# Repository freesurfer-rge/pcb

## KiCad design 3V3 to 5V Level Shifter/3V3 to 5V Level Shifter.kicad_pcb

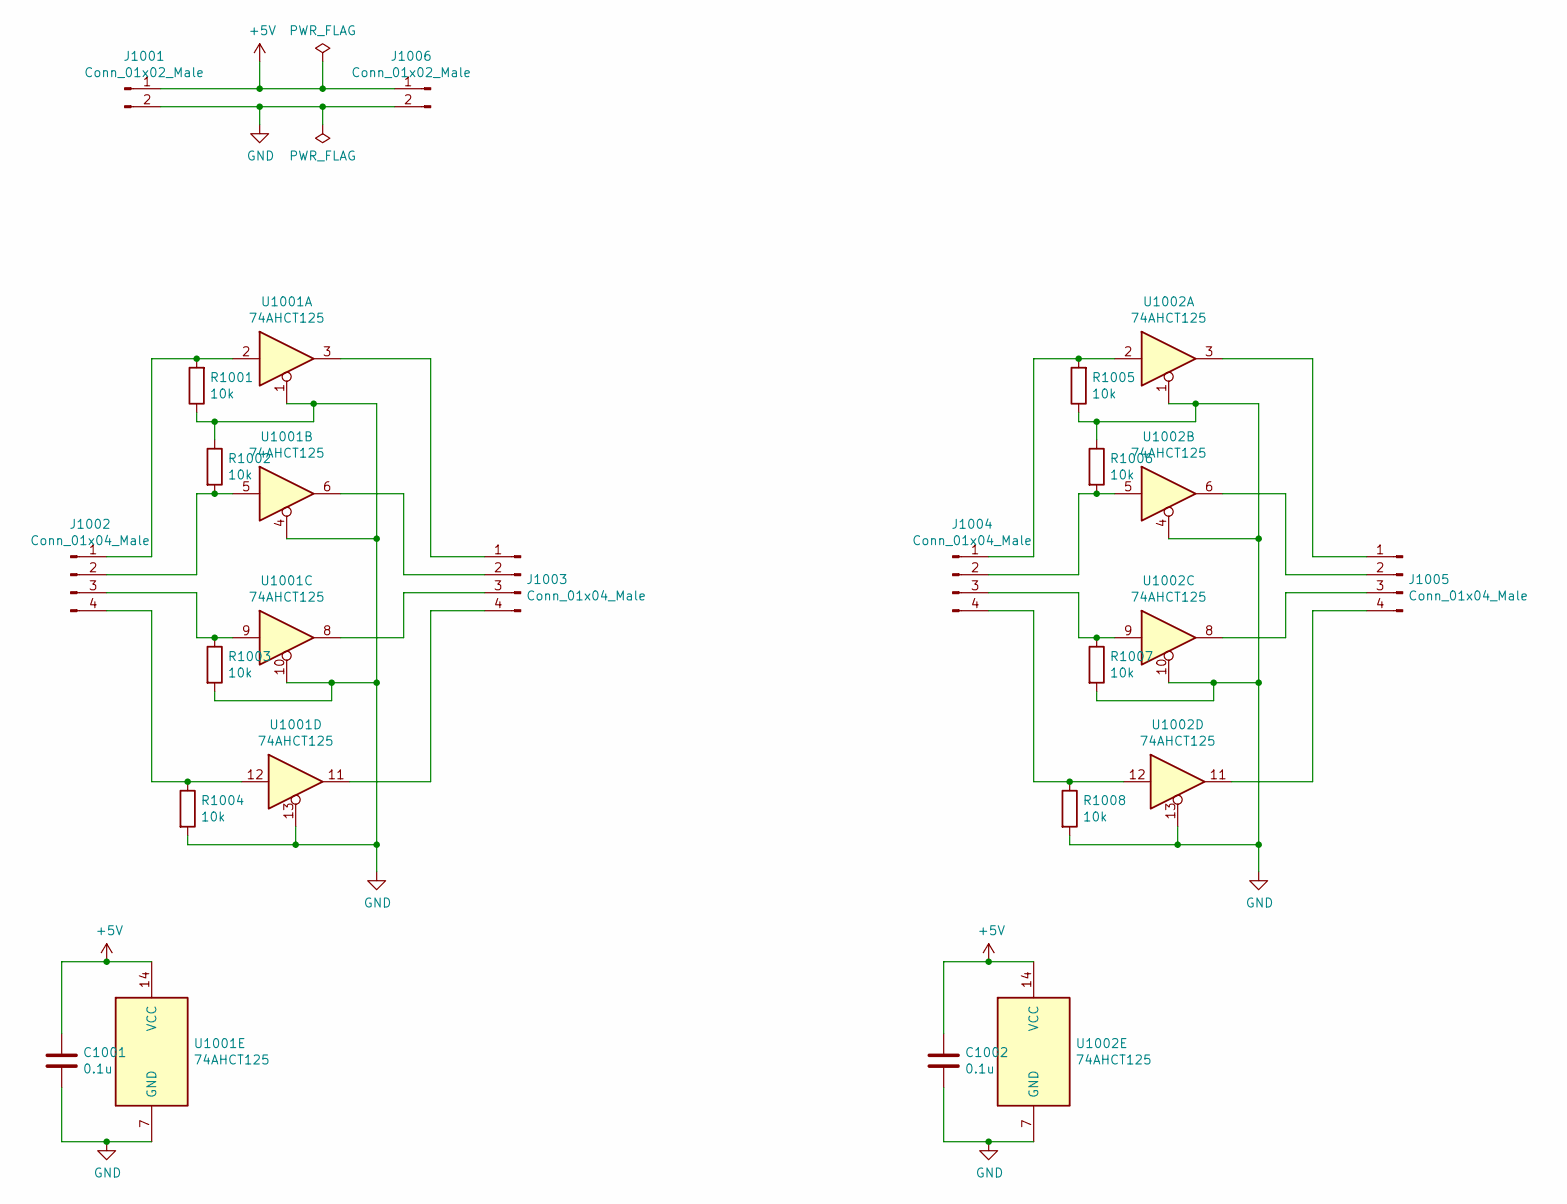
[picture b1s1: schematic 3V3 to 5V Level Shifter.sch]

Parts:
C1001, C1002: 0.1u; C_Disc_D4.7mm_W2.5mm_P5.00mm
J1001, J1006: Conn_01x02_Male; PinHeader_1x02_P2.54mm_Vertical
J1002, J1003, J1004, J1005: Conn_01x04_Male; PinHeader_1x04_P2.54mm_Vertical
R1001, R1002, R1003, R1004, R1005, R1006, R1007, R1008: 10k; R_Axial_DIN0207_L6.3mm_D2.5mm_P7.62mm_Horizontal
U1001, U1002: 74AHCT125; DIP-14_W7.62mm_Socket

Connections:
+5V: C1001.2, C1002.2, J1001.1, J1006.1, U1001.14 (VCC), U1002.14 (VCC)
GND: C1001.1, C1002.1, J1001.2, J1006.2, R1001.1, R1002.1, R1003.2, R1004.2, R1005.1, R1006.1, R1007.2, R1008.2, U1001.1, U1001.4, U1001.7 (GND), U1001.10, U1001.13, U1002.1, U1002.4, U1002.7 (GND), U1002.10, U1002.13
unnamed: J1002.1, R1001.2, U1001.2
unnamed: J1002.2, R1002.2, U1001.5
unnamed: J1002.3, R1003.1, U1001.9
unnamed: J1002.4, R1004.1, U1001.12
unnamed: J1003.1, U1001.3
unnamed: J1003.2, U1001.6
unnamed: J1003.3, U1001.8
unnamed: J1003.4, U1001.11
unnamed: J1004.1, R1005.2, U1002.2
unnamed: J1004.2, R1006.2, U1002.5
unnamed: J1004.3, R1007.1, U1002.9
unnamed: J1004.4, R1008.1, U1002.12
unnamed: J1005.1, U1002.3
unnamed: J1005.2, U1002.6
unnamed: J1005.3, U1002.8
unnamed: J1005.4, U1002.11

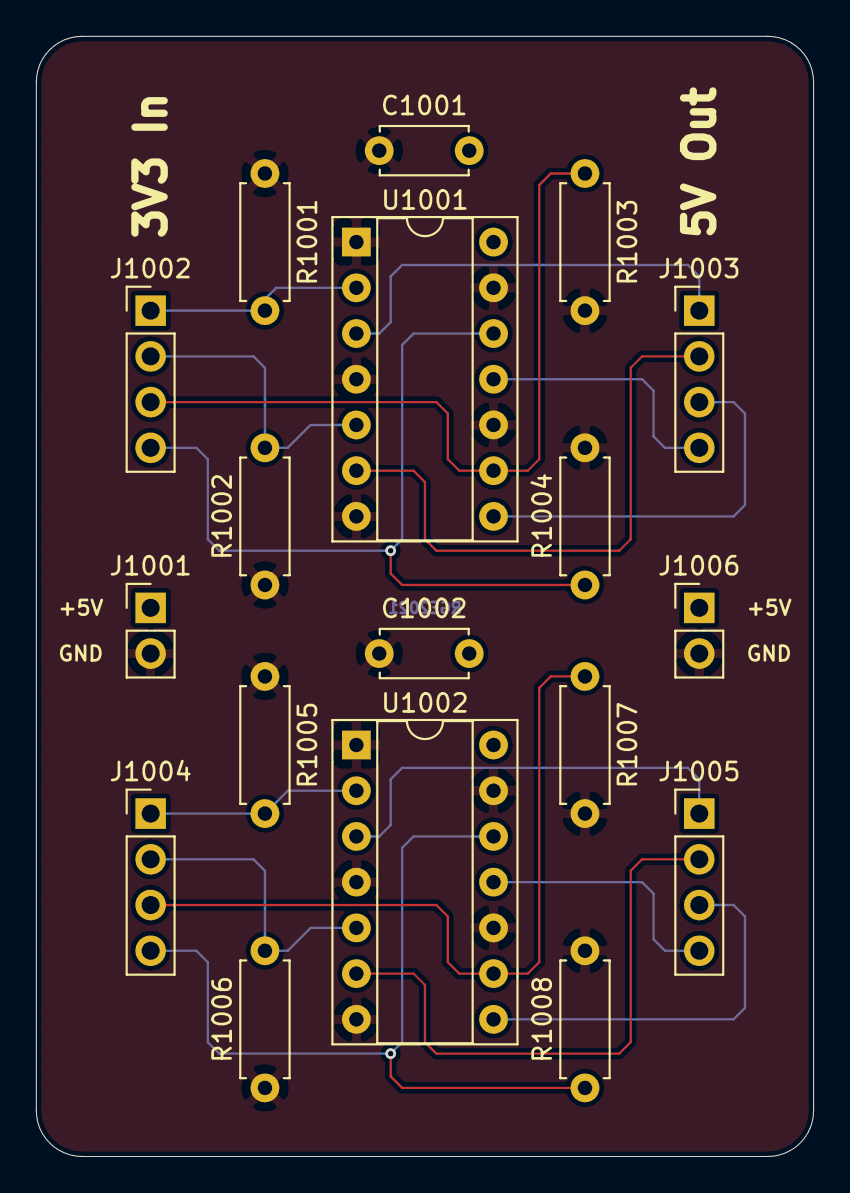
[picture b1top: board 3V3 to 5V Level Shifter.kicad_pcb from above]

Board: 2 copper layers, 43.2 x 62.2 mm, 18 parts (0 on the bottom side), 18 nets.

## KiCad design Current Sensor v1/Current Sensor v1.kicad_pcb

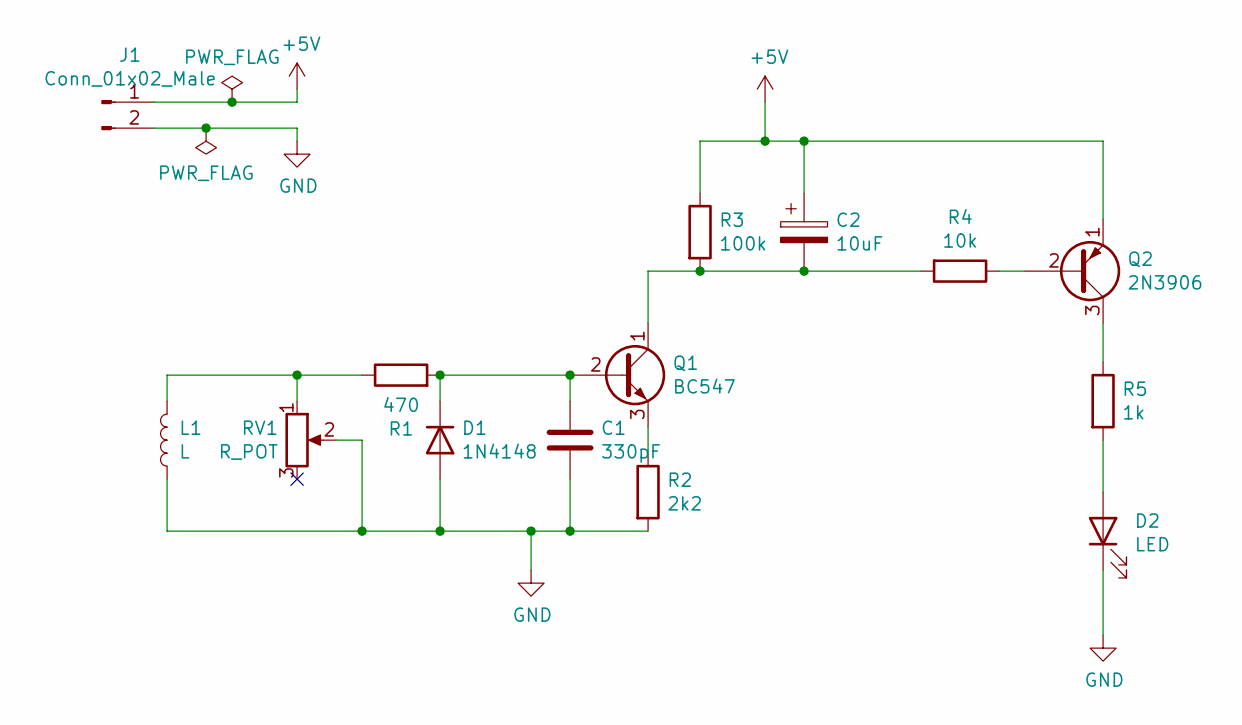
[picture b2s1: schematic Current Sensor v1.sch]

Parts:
C1: 330pF; C_Disc_D3.0mm_W2.0mm_P2.50mm
C2: 10uF; CP_Radial_D4.0mm_P1.50mm
D1: 1N4148; D_DO-35_SOD27_P7.62mm_Horizontal
D2: LED; LED_D5.0mm
J1: Conn_01x02_Male; PinHeader_1x02_P2.54mm_Vertical
L1: L; L_CS1050
Q1: BC547; TO-92_Inline_Wide
Q2: 2N3906; TO-92_Wide
R1: 470; R_Axial_DIN0207_L6.3mm_D2.5mm_P7.62mm_Horizontal
R2: 2k2; R_Axial_DIN0207_L6.3mm_D2.5mm_P7.62mm_Horizontal
R3: 100k; R_Axial_DIN0207_L6.3mm_D2.5mm_P7.62mm_Horizontal
R4: 10k; R_Axial_DIN0207_L6.3mm_D2.5mm_P7.62mm_Horizontal
R5: 1k; R_Axial_DIN0207_L6.3mm_D2.5mm_P7.62mm_Horizontal
RV1: R_POT; Potentiometer_Piher_PT-10-V10_Vertical

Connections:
+5V: C2.1, J1.1, Q2.1 (E), R3.1
GND: C1.2, D1.2 (A), D2.1 (K), J1.2, L1.1, R2.2, RV1.2
unnamed: C1.1, D1.1 (K), Q1.2 (B), R1.2
unnamed: C2.2, Q1.1 (C), R3.2, R4.2
unnamed: D2.2 (A), R5.2
unnamed: L1.2, R1.1, RV1.1
unnamed: Q1.3 (E), R2.1
unnamed: Q2.2 (B), R4.1
unnamed: Q2.3 (C), R5.1

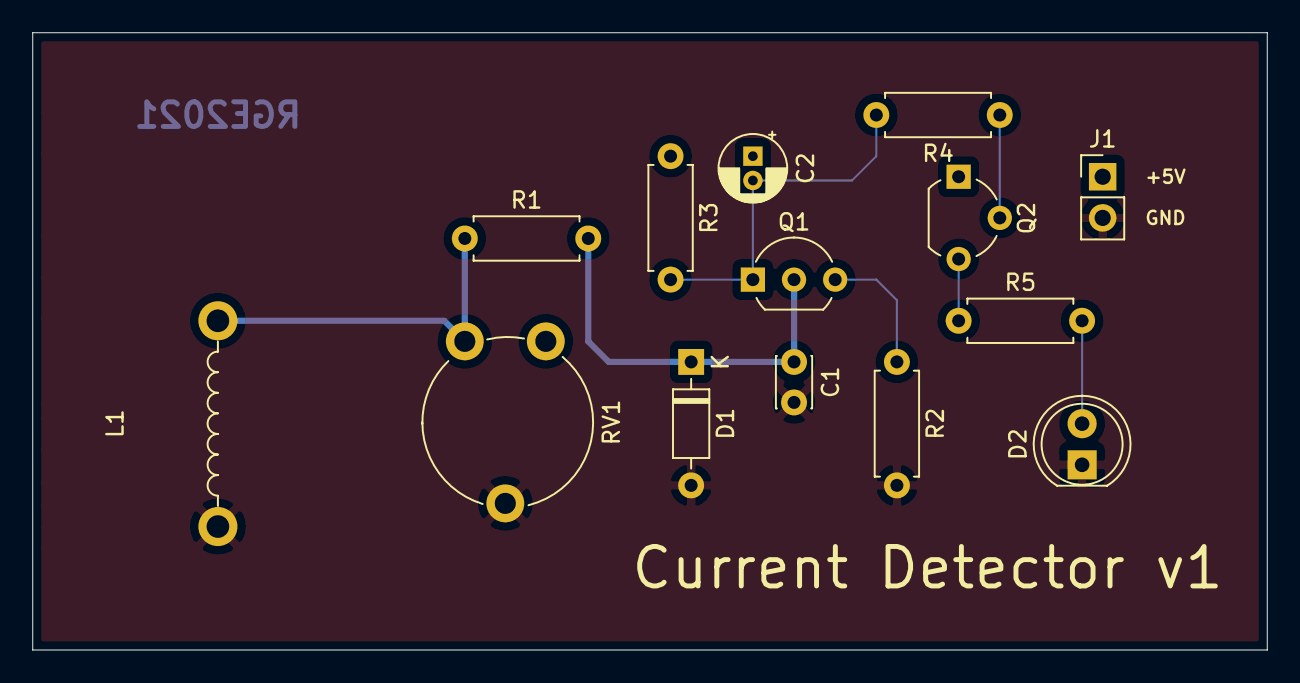
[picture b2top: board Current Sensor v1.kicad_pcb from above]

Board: 2 copper layers, 76.2 x 38.1 mm, 14 parts (0 on the bottom side), 9 nets.

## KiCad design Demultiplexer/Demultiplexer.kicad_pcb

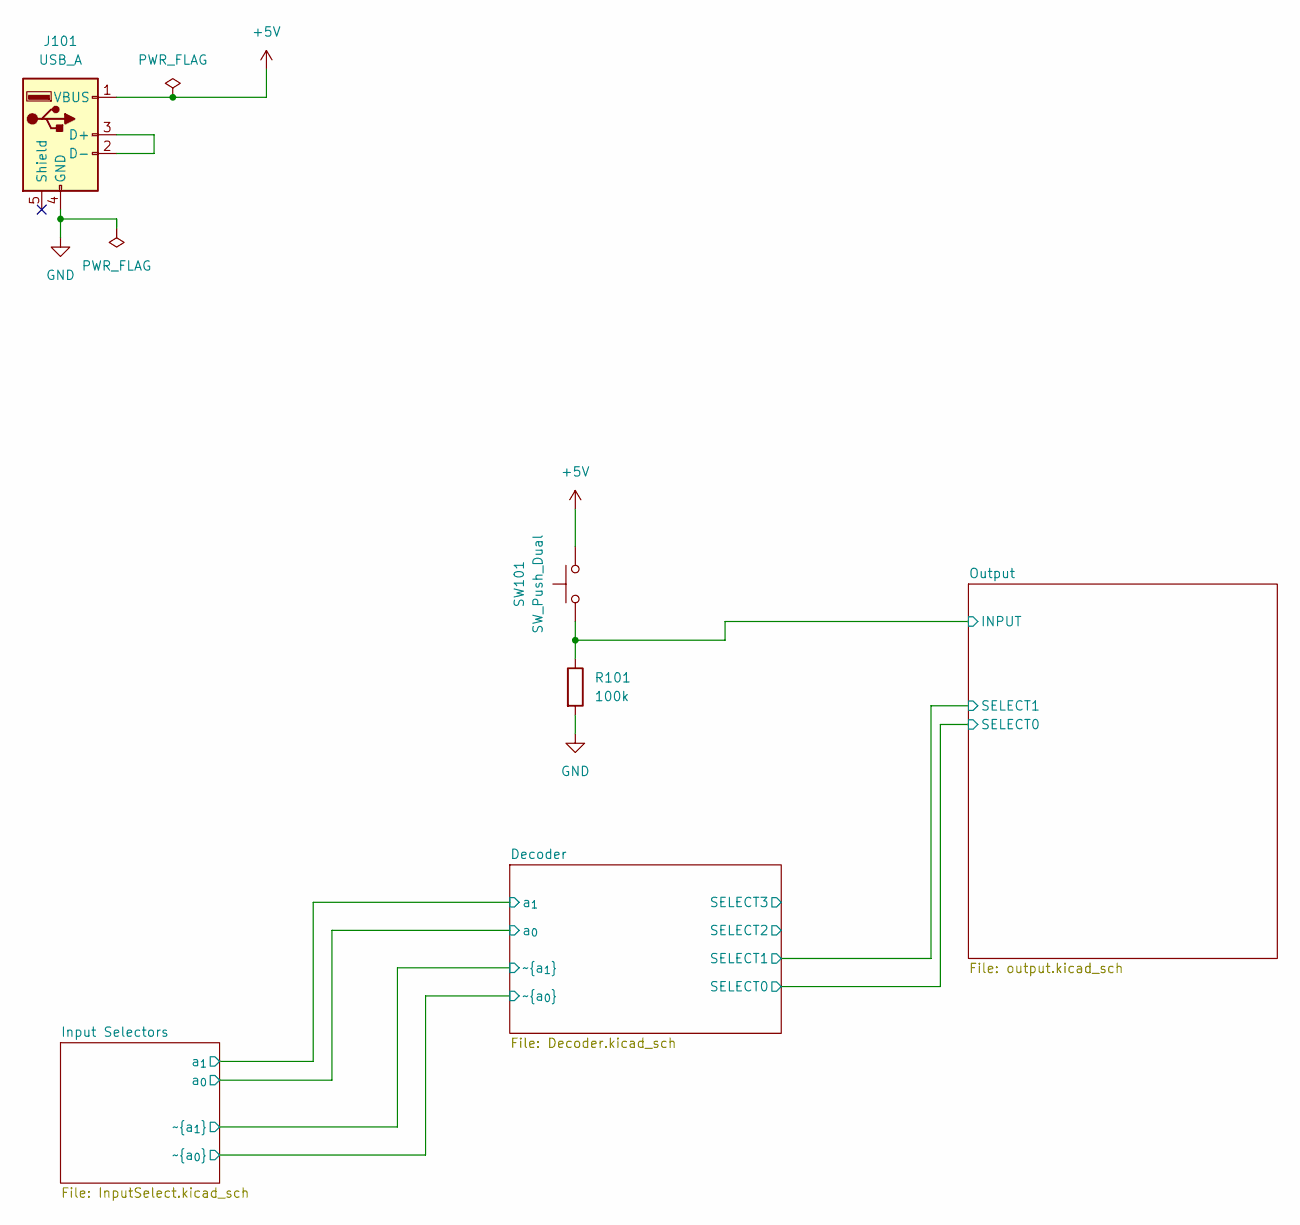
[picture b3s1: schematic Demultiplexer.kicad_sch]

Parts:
J101: USB_A; USB_A_Molex_67643_Horizontal
R101: 100k; R_Axial_DIN0207_L6.3mm_D2.5mm_P7.62mm_Horizontal
SW101: SW_Push_Dual; SW_PUSH_6mm_H4.3mm

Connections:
+5V: J101.1 (VBUS), SW101.2; also elsewhere on the board
/Output/INPUT: R101.1, SW101.1; also elsewhere on the board
GND: J101.4 (GND), R101.2; also elsewhere on the board
unnamed: J101.2 (D-), J101.3 (D+)

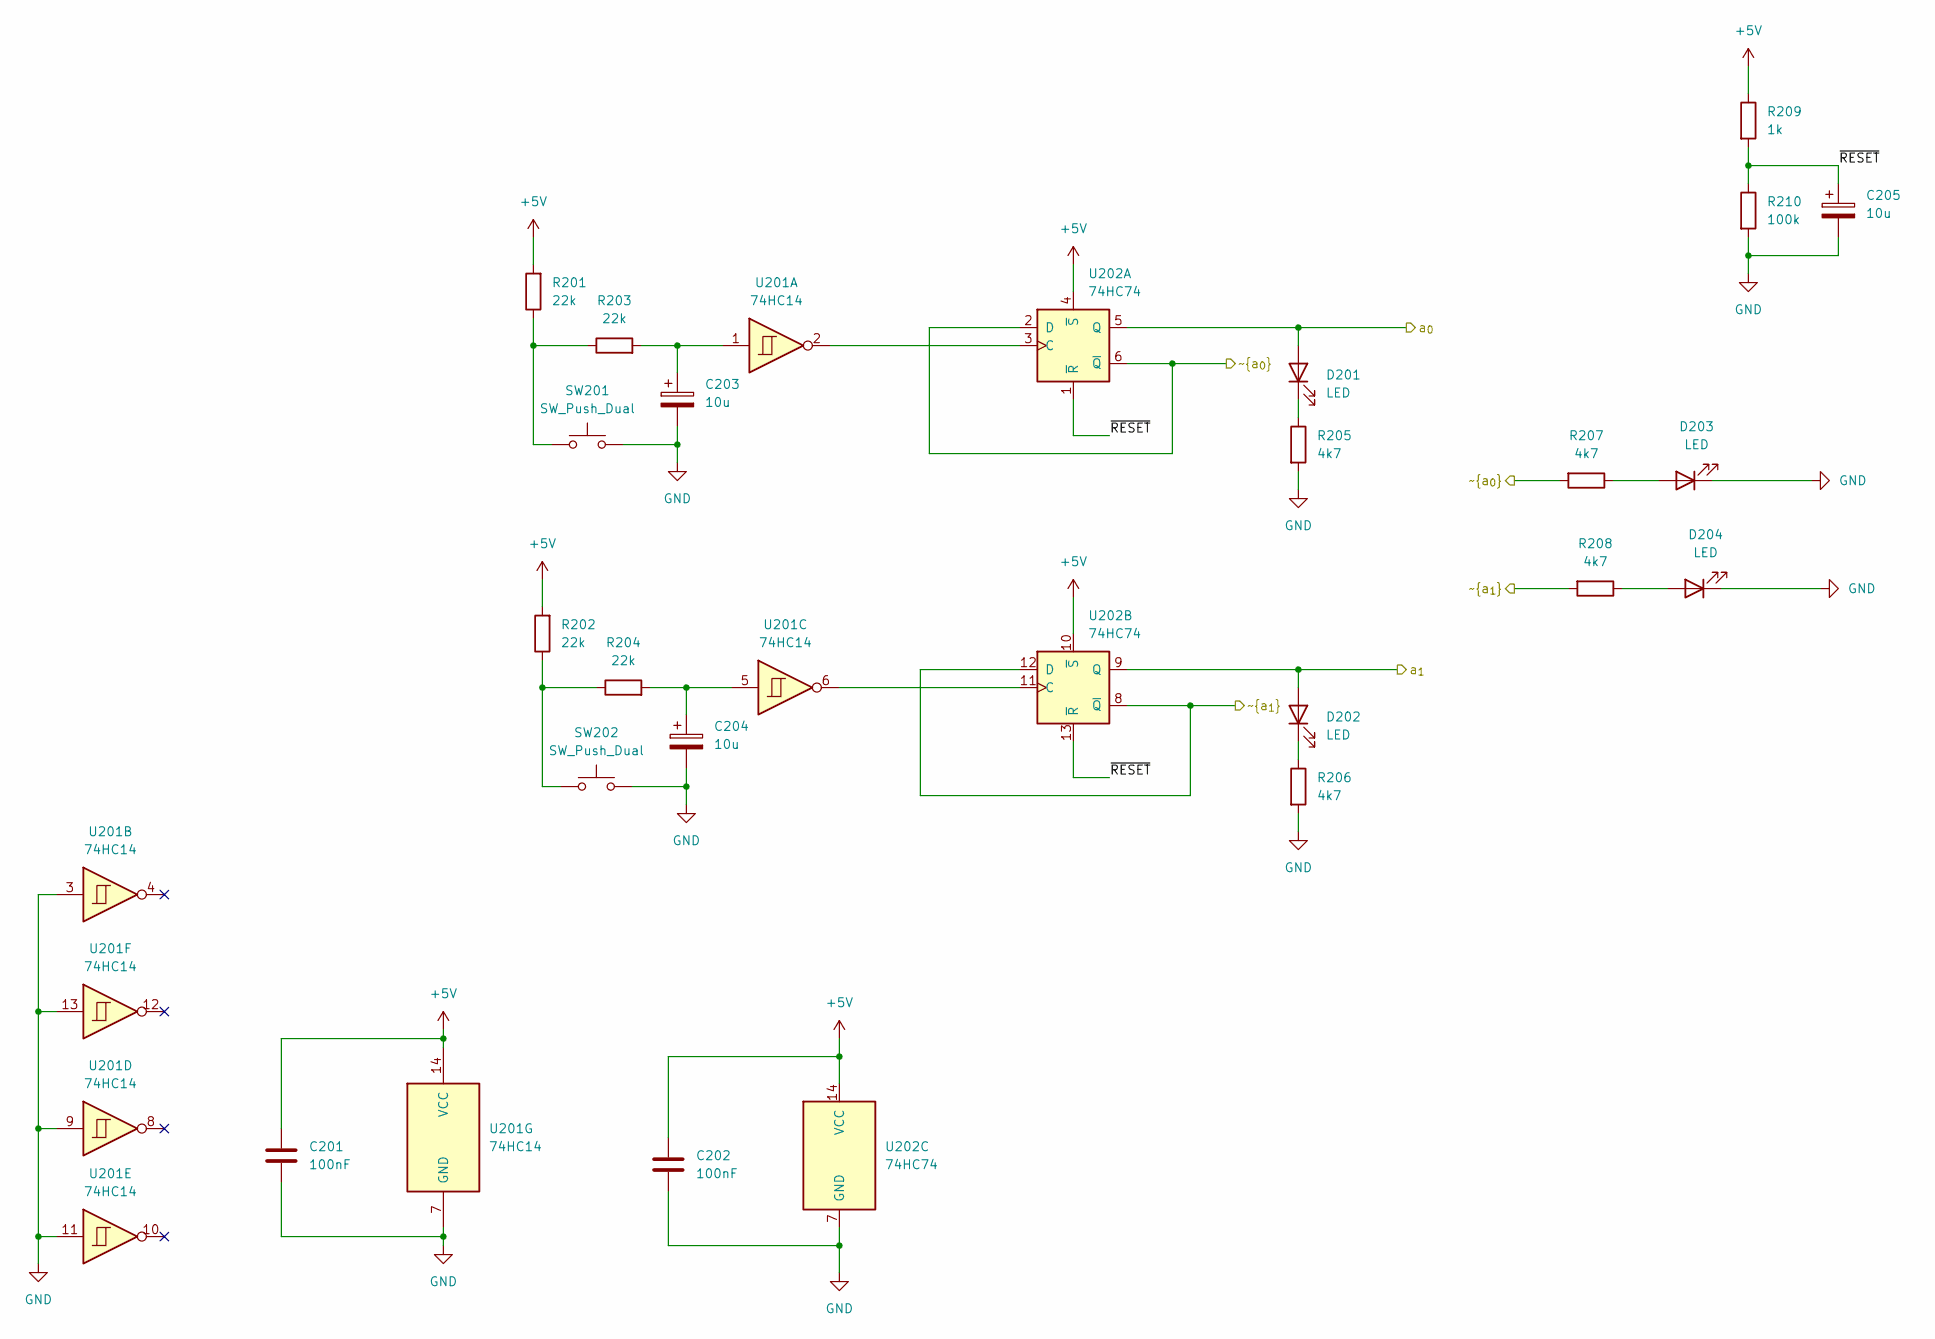
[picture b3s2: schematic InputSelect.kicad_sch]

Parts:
C201, C202: 100nF; C_Disc_D5.0mm_W2.5mm_P5.00mm
C203, C204, C205: 10u; CP_Radial_D4.0mm_P1.50mm
D201, D202: LED; LED_D5.0mm
D203, D204: LED; LED_D3.0mm
R201, R202, R203, R204: 22k; R_Axial_DIN0207_L6.3mm_D2.5mm_P7.62mm_Horizontal
R205, R206, R207, R208: 4k7; R_Axial_DIN0207_L6.3mm_D2.5mm_P7.62mm_Horizontal
R209: 1k; R_Axial_DIN0207_L6.3mm_D2.5mm_P7.62mm_Horizontal
R210: 100k; R_Axial_DIN0207_L6.3mm_D2.5mm_P7.62mm_Horizontal
SW201, SW202: SW_Push_Dual; SW_PUSH_6mm_H4.3mm
U201: 74HC14
U202: 74HC74; DIP-14_W7.62mm_Socket

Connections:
+5V: C201.2, C202.2, R201.2, R202.2, R209.1, U201.14 (VCC), U202.4 (~S), U202.10 (~S), U202.14 (VCC); also elsewhere on the board
/Decoder/a_{0}: D201.2 (A), U202.5 (Q); also elsewhere on the board
/Decoder/a_{1}: D202.2 (A), U202.9 (Q); also elsewhere on the board
/Decoder/~a_{0}: R207.2, U202.2 (D), U202.6 (~Q); also elsewhere on the board
/Decoder/~a_{1}: R208.2, U202.8 (~Q), U202.12 (D); also elsewhere on the board
/Input Selectors/~RESET: C205.1, R209.2, R210.1, U202.1 (~R), U202.13 (~R)
GND: C201.1, C202.1, C203.2, C204.2, C205.2, D203.1 (K), D204.1 (K), R205.2, R206.2, R210.2, SW201.2, SW202.2, U201.3, U201.7 (GND), U201.9, U201.11, U201.13, U202.7 (GND); also elsewhere on the board
unnamed: C203.1, R203.2, U201.1
unnamed: C204.1, R204.2, U201.5
unnamed: D201.1 (K), R205.1
unnamed: D202.1 (K), R206.1
unnamed: D203.2 (A), R207.1
unnamed: D204.2 (A), R208.1
unnamed: R201.1, R203.1, SW201.1
unnamed: R202.1, R204.1, SW202.1
unnamed: U201.2, U202.3 (C)
unnamed: U201.6, U202.11 (C)

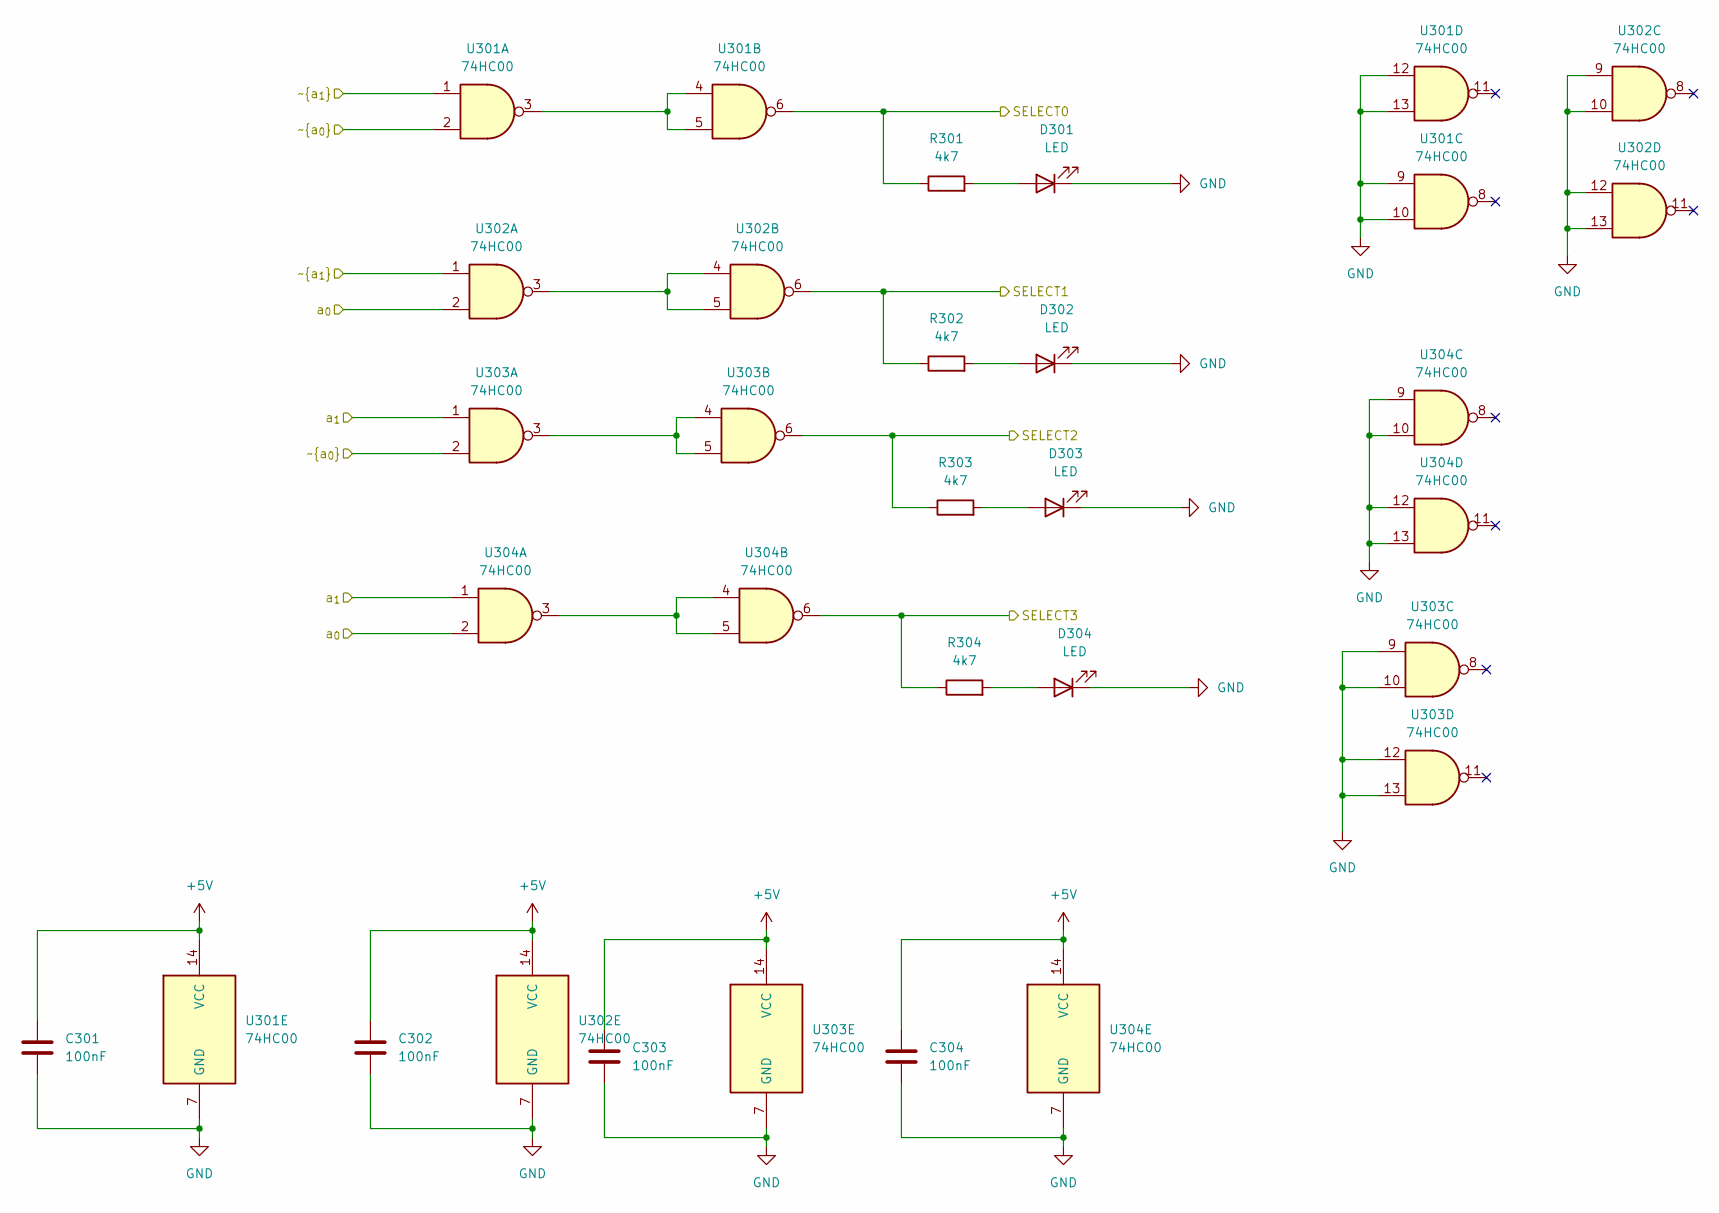
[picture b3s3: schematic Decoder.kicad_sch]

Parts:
C301, C302, C303, C304: 100nF; C_Disc_D5.0mm_W2.5mm_P5.00mm
D301, D302, D303, D304: LED; LED_D3.0mm
R301, R302, R303, R304: 4k7; R_Axial_DIN0207_L6.3mm_D2.5mm_P7.62mm_Horizontal
U301, U302, U303, U304: 74HC00; DIP-14_W7.62mm_Socket

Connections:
+5V: C301.2, C302.2, C303.2, C304.2, U301.14 (VCC), U302.14 (VCC), U303.14 (VCC), U304.14 (VCC); also elsewhere on the board
/Decoder/a_{0}: U302.2, U304.2; also elsewhere on the board
/Decoder/a_{1}: U303.1, U304.1; also elsewhere on the board
/Decoder/~a_{0}: U301.2, U303.2; also elsewhere on the board
/Decoder/~a_{1}: U301.1, U302.1; also elsewhere on the board
GND: C301.1, C302.1, C303.1, C304.1, D301.1 (K), D302.1 (K), D303.1 (K), D304.1 (K), U301.7 (GND), U301.9, U301.10, U301.12, U301.13, U302.7 (GND), U302.9, U302.10, U302.12, U302.13, U303.7 (GND), U303.9, U303.10, U303.12, U303.13, U304.7 (GND), U304.9, U304.10, U304.12, U304.13; also elsewhere on the board
unnamed: D301.2 (A), R301.2
unnamed: D302.2 (A), R302.2
unnamed: D303.2 (A), R303.2
unnamed: D304.2 (A), R304.2
unnamed: U301.3, U301.4, U301.5
unnamed: U302.3, U302.4, U302.5
unnamed: U303.3, U303.4, U303.5
unnamed: U304.3, U304.4, U304.5

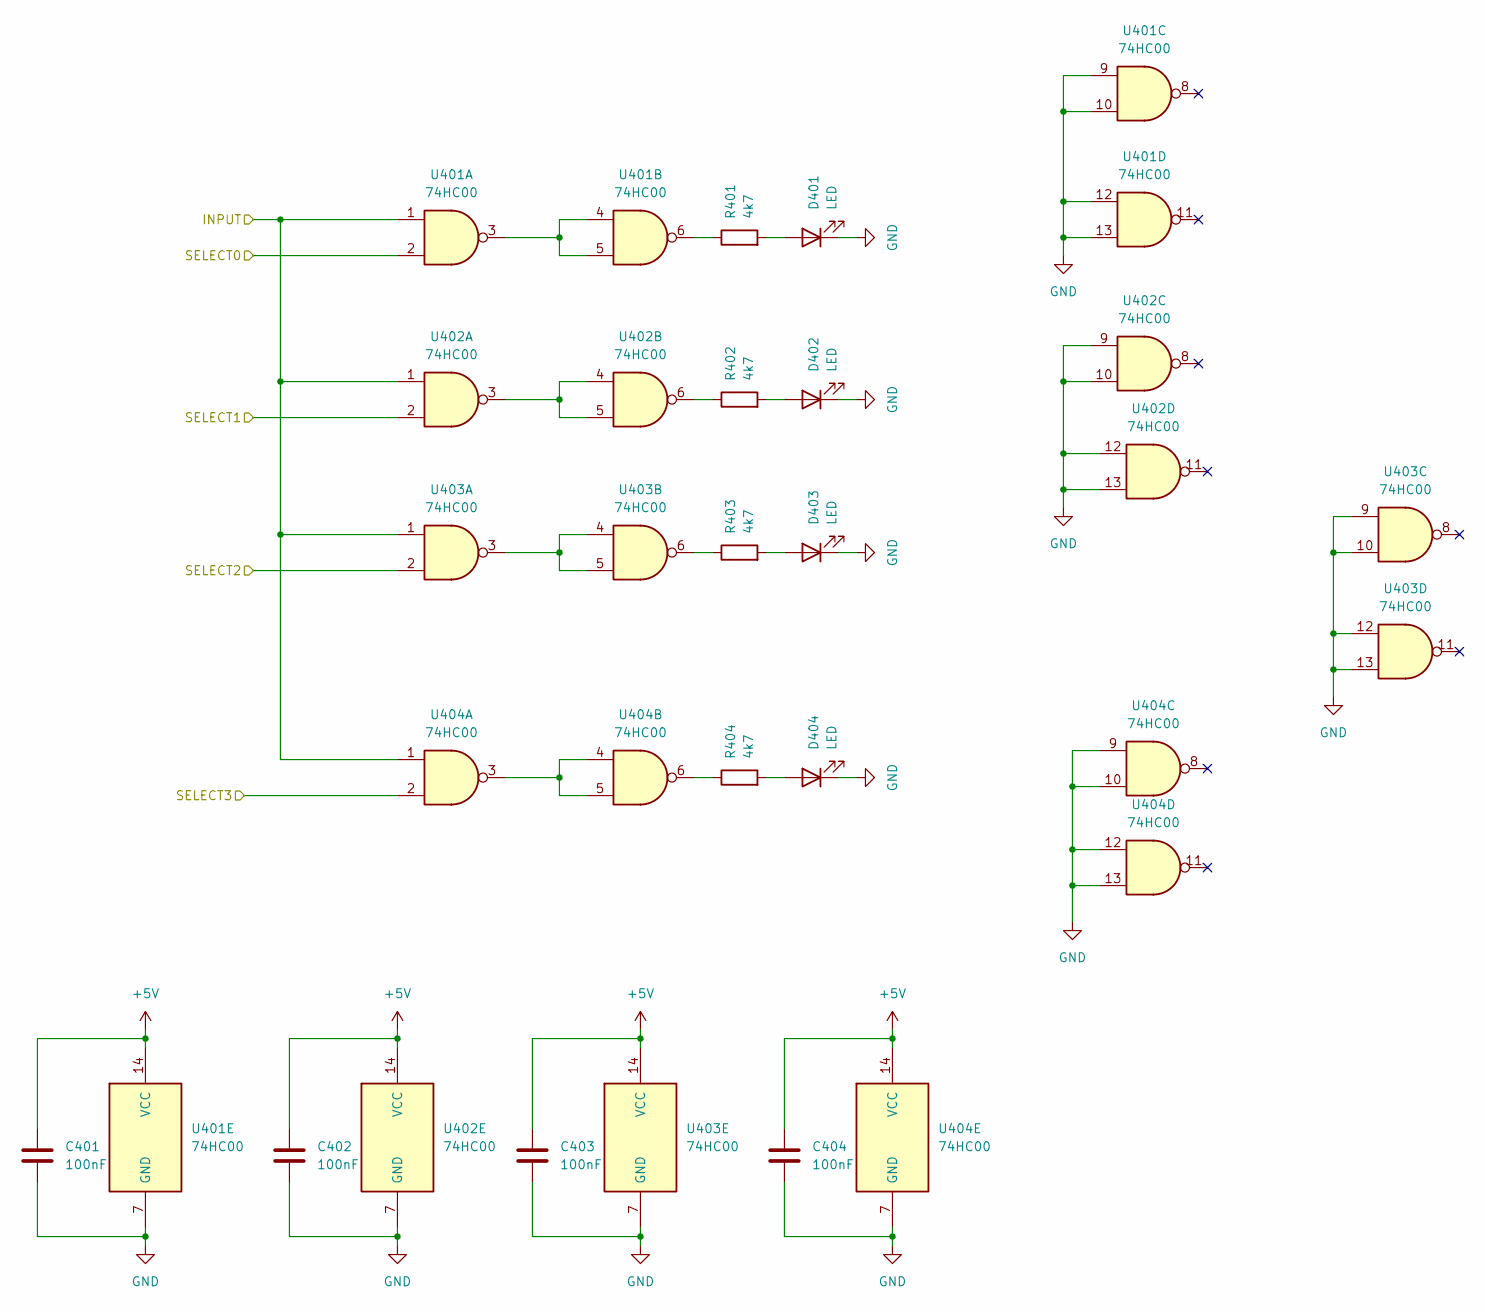
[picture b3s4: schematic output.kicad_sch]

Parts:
C401, C402, C403, C404: 100nF; C_Disc_D5.0mm_W2.5mm_P5.00mm
D401, D402, D403, D404: LED; LED_D5.0mm
R401, R402, R403, R404: 4k7; R_Axial_DIN0207_L6.3mm_D2.5mm_P7.62mm_Horizontal
U401, U402, U404: 74HC00; DIP-14_W7.62mm_Socket
U403: 74HC00

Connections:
+5V: C401.2, C402.2, C403.2, C404.2, U401.14 (VCC), U402.14 (VCC), U403.14 (VCC), U404.14 (VCC); also elsewhere on the board
/Output/INPUT: U401.2, U402.2, U403.2, U404.2; also elsewhere on the board
GND: C401.1, C402.1, C403.1, C404.1, D401.1 (K), D402.1 (K), D403.1 (K), D404.1 (K), U401.7 (GND), U401.9, U401.10, U401.12, U401.13, U402.7 (GND), U402.9, U402.10, U402.12, U402.13, U403.7 (GND), U403.9, U403.10, U403.12, U403.13, U404.7 (GND), U404.9, U404.10, U404.12, U404.13; also elsewhere on the board
unnamed: D401.2 (A), R401.2
unnamed: D402.2 (A), R402.2
unnamed: D403.2 (A), R403.2
unnamed: D404.2 (A), R404.2
unnamed: R401.1, U401.6
unnamed: R402.1, U402.6
unnamed: R403.1, U403.6
unnamed: R404.1, U404.6
unnamed: U401.3, U401.4, U401.5
unnamed: U402.3, U402.4, U402.5
unnamed: U403.3, U403.4, U403.5
unnamed: U404.3, U404.4, U404.5

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
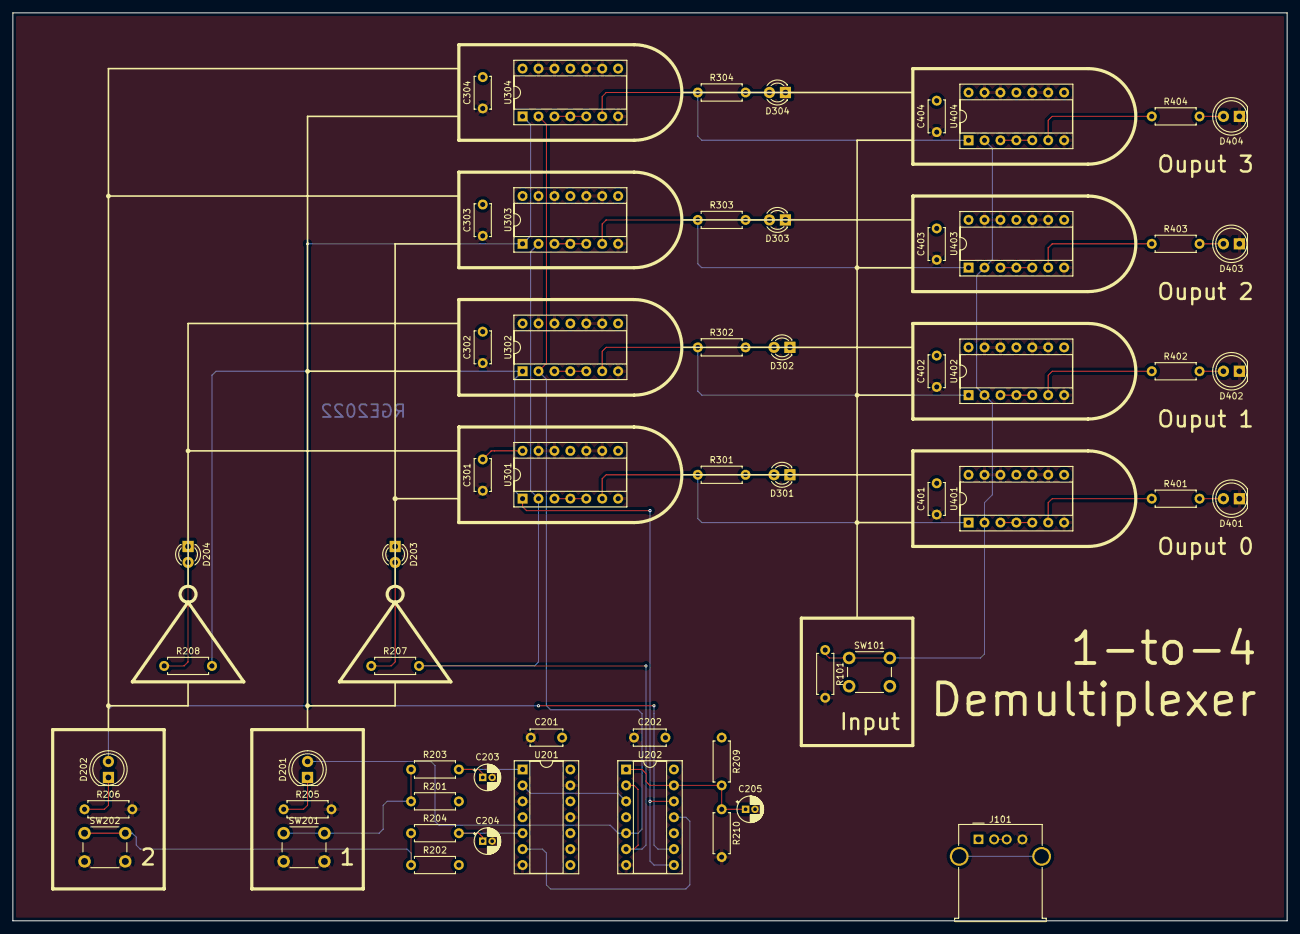
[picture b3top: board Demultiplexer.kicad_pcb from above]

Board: 2 copper layers, 203.2 x 144.8 mm, 58 parts (0 on the bottom side), 43 nets.

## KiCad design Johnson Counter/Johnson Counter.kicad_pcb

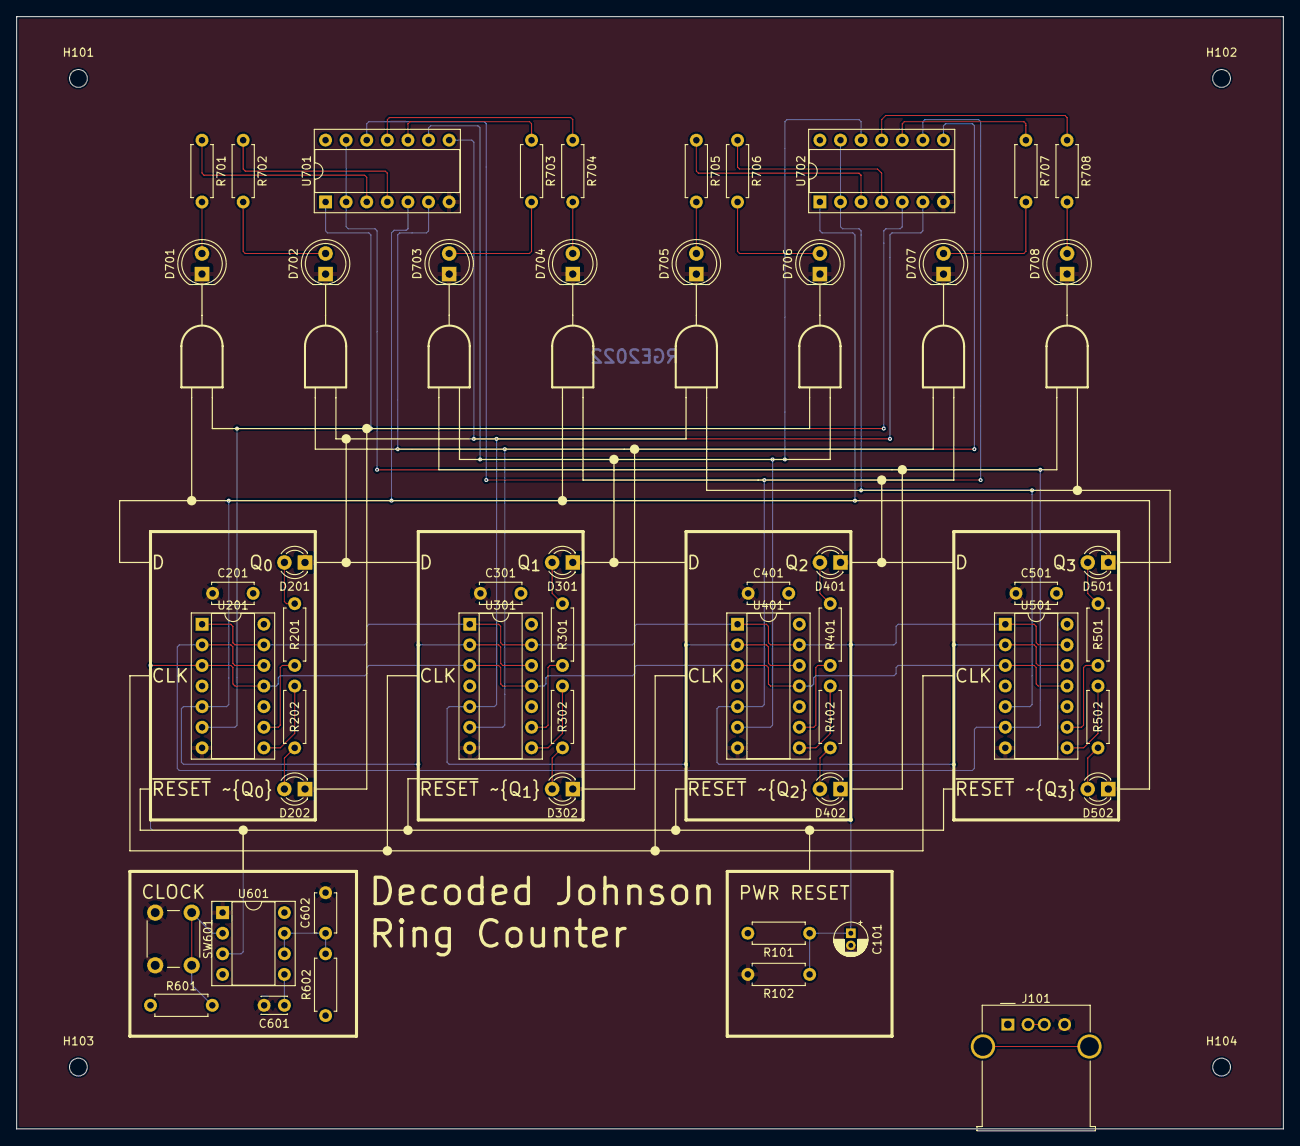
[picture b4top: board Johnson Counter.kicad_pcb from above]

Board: 2 copper layers, 156.2 x 137.2 mm, 56 parts (0 on the bottom side), 48 nets.

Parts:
C101: 10u; CP_Radial_D4.0mm_P1.50mm
C201, C301, C401, C501: 100n; C_Disc_D5.0mm_W2.5mm_P5.00mm
C601: 10nF; C_Disc_D3.0mm_W2.0mm_P2.50mm
C602: 0.1u; C_Disc_D4.7mm_W2.5mm_P5.00mm
D201, D202, D301, D302, D401, D402, D501, D502: LED; LED_D3.0mm
D701, D702, D703, D704, D705, D706, D707, D708: LED; LED_D5.0mm
H101, H102, H103, H104: MountingHole; MountingHole_2.2mm_M2
J101: USB_A; USB_A_Molex_67643_Horizontal
R101: 1k; R_Axial_DIN0207_L6.3mm_D2.5mm_P7.62mm_Horizontal
R102: 100k; R_Axial_DIN0207_L6.3mm_D2.5mm_P7.62mm_Horizontal
R201, R202, R301, R302, R401, R402, R501, R502, R701, R702, R703, R704, R705, R706, R707, R708: 4k7; R_Axial_DIN0207_L6.3mm_D2.5mm_P7.62mm_Horizontal
R601: 22k; R_Axial_DIN0207_L6.3mm_D2.5mm_P7.62mm_Horizontal
R602: 1M; R_Axial_DIN0207_L6.3mm_D2.5mm_P7.62mm_Horizontal
SW601: SW_Push; SW_PUSH_6mm_H4.3mm
U201, U301, U401, U501: 74HC74; DIP-14_W7.62mm_Socket
U601: LM555xM; DIP-8_W7.62mm_Socket
U701, U702: 4081; DIP-14_W7.62mm_Socket

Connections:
+5V: C201.2, C301.2, C401.2, C501.2, J101.1 (VBUS), R101.2, R601.1, R602.1, U201.4 (~S), U201.10 (~S), U201.14 (VCC), U301.4 (~S), U301.10 (~S), U301.14 (VCC), U401.4 (~S), U401.10 (~S), U401.14 (VCC), U501.4 (~S), U501.10 (~S), U501.14 (VCC), U601.4 (R), U601.8 (VCC), U701.14 (VDD), U702.14 (VDD)
/CLOCK: U201.3 (C), U201.11 (C), U301.3 (C), U301.11 (C), U401.3 (C), U401.11 (C), U501.3 (C), U501.11 (C), U601.3 (Q)
/Decoder/Out0: D701.2 (A), R701.2
/Decoder/Out1: D702.2 (A), R702.2
/Decoder/Out2: D703.2 (A), R703.2
/Decoder/Out3: D704.2 (A), R704.2
/Decoder/Out4: D705.2 (A), R705.2
/Decoder/Out5: D706.2 (A), R706.2
/Decoder/Out6: D707.2 (A), R707.2
/Decoder/Out7: D708.2 (A), R708.2
/Q_{0}: U201.5 (Q), U301.2 (D), U301.12 (D), U701.5, U702.1
/Q_{1}: U301.5 (Q), U401.2 (D), U401.12 (D), U701.8, U702.6
/Q_{2}: U401.5 (Q), U501.2 (D), U501.12 (D), U701.12, U702.9
/Q_{3}: U501.5 (Q), U702.2, U702.13
/~Q_{0}: U201.6 (~Q), U701.1, U702.5
/~Q_{1}: U301.6 (~Q), U701.6, U702.8
/~Q_{2}: U401.6 (~Q), U701.9, U702.12
/~Q_{3}: U201.2 (D), U201.12 (D), U501.6 (~Q), U701.2, U701.13
/~RESET: C101.1, R101.1, R102.1, U201.1 (~R), U201.13 (~R), U301.1 (~R), U301.13 (~R), U401.1 (~R), U401.13 (~R), U501.1 (~R), U501.13 (~R)
GND: C101.2, C201.1, C301.1, C401.1, C501.1, C601.2, C602.2, D201.1 (K), D202.1 (K), D301.1 (K), D302.1 (K), D401.1 (K), D402.1 (K), D501.1 (K), D502.1 (K), D701.1 (K), D702.1 (K), D703.1 (K), D704.1 (K), D705.1 (K), D706.1 (K), D707.1 (K), D708.1 (K), J101.4 (GND), R102.2, SW601.2, U201.7 (GND), U301.7 (GND), U401.7 (GND), U501.7 (GND), U601.1 (GND), U701.7 (VSS), U702.7 (VSS)
unnamed: D201.2 (A), R201.2
unnamed: D202.2 (A), R202.2
unnamed: D301.2 (A), R301.2
unnamed: D302.2 (A), R302.2
unnamed: D401.2 (A), R401.2
unnamed: D402.2 (A), R402.2
unnamed: D501.2 (A), R501.2
unnamed: D502.2 (A), R502.2
unnamed: J101.2 (D-), J101.3 (D+)
unnamed: R201.1, U201.9 (Q)
unnamed: R202.1, U201.8 (~Q)
unnamed: R301.1, U301.9 (Q)
unnamed: R302.1, U301.8 (~Q)
unnamed: R401.1, U401.9 (Q)
unnamed: R402.1, U401.8 (~Q)
unnamed: R501.1, U501.9 (Q)
unnamed: R502.1, U501.8 (~Q)
unnamed: R601.2, SW601.1, U601.2 (TR)
unnamed: C602.1, R602.2, U601.6 (THR), U601.7 (DIS)
unnamed: R701.1, U701.3
unnamed: R702.1, U701.4
unnamed: R703.1, U701.10
unnamed: R704.1, U701.11
unnamed: R705.1, U702.3
unnamed: R706.1, U702.4
unnamed: R707.1, U702.10
unnamed: R708.1, U702.11
unnamed: C601.1, U601.5 (CV)
